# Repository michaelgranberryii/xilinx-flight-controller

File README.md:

# Xilinx Zynq-7000 Flight Controller 

This is a custom flight controller for a quadcopter drone, implemented on a Zynq-7000 SoC on the [Zybo Z7-10 FPGA SoC Development Board](https://digilent.com/shop/zybo-z7-zynq-7000-arm-fpga-soc-development-board/?gad_source=1&gclid=Cj0KCQiAkeSsBhDUARIsAK3tiedDBNo96Tg5VWCeuEqzXgPKJSFg8GQ0qwLCV-v5TlTKltLerrQGLDkaAjBgEALw_wcB). The flight controller uses PID controllers along with a [MPU-6050 | 3 Axis Accelerometer Gyroscope ](https://www.amazon.com/HiLetgo-MPU-6050-Accelerometer-Gyroscope-Converter/dp/B01DK83ZYQ?th=1) for flight stability. Two flight modes are available: Rate Mode (Acro Mode) which uses a single loop PID controller and Stabilize Mode (Self-Leveling Mode) which uses a dual loop PID controller.

## Dependencies

### Hardware

* [Zybo Z7-10 FPGA SoC Development Board](https://digilent.com/shop/zybo-z7-zynq-7000-arm-fpga-soc-development-board/?gad_source=1&gclid=Cj0KCQiAkeSsBhDUARIsAK3tiedDBNo96Tg5VWCeuEqzXgPKJSFg8GQ0qwLCV-v5TlTKltLerrQGLDkaAjBgEALw_wcB)
* [MPU-6050 | 3 Axis Accelerometer Gyroscope ](https://www.amazon.com/HiLetgo-MPU-6050-Accelerometer-Gyroscope-Converter/dp/B01DK83ZYQ?th=1)
* [Radiolink T8FB 8 Channels 2.4GHz RC Remote Transmitter and R8EF Receiver](https://www.amazon.com/Radiolink-Transmitter-Receiver-2-4GHz-Controller/dp/B07DPK9Q9X/ref=sr_1_8?crid=34H23UYBP2SKA&dib=eyJ2IjoiMSJ9.DPB_D_-uXEtxyzGycjiEyngkkrfimBVfbW4ewKRMgHdWoZd8kxR5b7jw0f5nMZls2Qb6V5CaN3ZfWsz7HZxhJrX90tzAb0QPEJUbYPUGGb2kpEbRmFlTLI2P86QUEIuNXMQfID7UFSSD-5kdgcvyu__B-VTDg-fb5czwKHN0Wl5XwdQDziz_BhiWEbAXvPp5PIw9FovmLC-oN_uPQwk0yAiQCDHy_djiuKr69YO0ViHIPJ16aY1Z_osZuZJMaIu-6asyX8v1I-ymjkhxUaAazSm7HCGohjngMDOZZgtEtbo.cCZTWbZ4u9XV9URevBCROmEVp4g-vu0lXmYiJxgRPmQ&dib_tag=se&keywords=drone+transmitter+radiolink&qid=1708402155&sprefix=drone+transmitter+radiolink%2Caps%2C165&sr=8-8)
* [F450 Drone Frame](https://www.amazon.com/HAWKS-WORK-Quadcopter-Soldered-version/dp/B09YQ4G4ZZ/ref=sr_1_1_sspa?crid=3N3WTXPM9LDKL&dib=eyJ2IjoiMSJ9.4SM5ot4VWDgjLdCVw62C2yKGLYTUUuc3lbi4BrTFGE9lpAKh0yMmMXJ_HIy-w1ENHsgIOVhhmYWpFB1ATbVhs8RRjUUaeWzyVOR1N0ha3JY5y-i-1TJu3e379htrydVJESWKMowWwq3ruebfXOp-SGRewwEUEbb5dCo8WSYisElMiAdD_meuExWMUxu_mJaVYU8nyTCTg59dAqnkI0jdbjbaDX142WhmPunSSgKYpJLF43dOjwTOQLx0ovp_XpcfKXJkWCgRW7E7xXokXZvfmimUiE6o6ibQ7mAoeM-98c8.ubOFJzHZ3AU_jyVGw8lJqdBcv9VBNKbAPPYqhvaB-e4&dib_tag=se&keywords=f450%2Bdrone%2Bframe&qid=1708402234&sprefix=f450%2Bdrone%2Caps%2C195&sr=8-1-spons&sp_csd=d2lkZ2V0TmFtZT1zcF9hdGY&th=1)
* [30A RC Brushless Motor Electric Speed Controller](https://www.amazon.com/RC-Brushless-Electric-Controller-bullet/dp/B071GRSFBD/ref=sr_1_4?crid=JMXOMHTAUCHV&dib=eyJ2IjoiMSJ9.wcXRcC8u6WMTk321CJMspA4Bjo8WyvU7S9tdHj4XXrRZN6O7hHFl5kzbjSvzMTZ-En1jRhSm3J4cd7zgXAknn8JgPXHhCurCiWyFo9wgS5pcgzPpAIhjxL9Zowfe-L6ReOSvZWRXDYMergQ2oleuHK2eYooR3kCsa7zb9R_QjHrUg5n7qfPdMynH9s7QN47VYThoIomzGBI9prRIGsj_hF-og1T7GlsKNxmGigtNDy_M2_I7ierAaly00huwBsoYgW8GAUCkMK90ynJmFmaWF3O137GK70m53xuhO36fMbs.yiFtRNF5yDGhqlkxH_yx9H00WZNZ_0crOrciYLcckoY&dib_tag=se&keywords=30A%2BRC%2BBrushless%2BMotor%2BElectric%2BSpeed%2BController%2BESC%2B3A%2BUBEC%2Bwith%2BXT60%2B%26%2B3.5mm%2BBullet%2BPlugs&qid=1708402480&sprefix=30a%2Brc%2Bbrushless%2Bmotor%2Belectric%2Bspeed%2Bcontroller%2Besc%2B3a%2Bubec%2Bwith%2Bxt60%2B%26%2B3.5mm%2Bbullet%2Bplugs%2Caps%2C155&sr=8-4&th=1)
* [A2212 1000KV Brushless Motor](https://www.amazon.com/QWinOut-Brushless-Outrunner-Multi-Copter-Quadcopter/dp/B07CVDHQKS/ref=sr_1_1?crid=1G5IM8DKU8SIP&dib=eyJ2IjoiMSJ9._27XAJ6z8Xiract4kND7udNpiqoN_pQC9MedRzfhIFYGyRx9oyV5UhlLUdA22XvwF8kf8OSVQj0Fo-E9RT67TuAs-i4kOSFeHEzr5NU0mvVaUnKGs5Vf8deE6-NLwU4lUR9LpMEcDlGJF7BHMjlHVvMGppm1qU6BHaiMaZuR91UzML-gfybXsLUigy1LmJ-3tyF6_1ikHYOK8w0fWH6f9ZbS-gAenApGc8AXPPVziHve8GzoEiNgXvsa65UJDh4SNVLwRSYLvnt5_zQseZ6h8uqAZkQQI8VzSBp9jZAkarI.3QyAjjS6RmnuF1MkatmTFHBwq5IZlhVe7zZr4WBPnxk&dib_tag=se&keywords=QWinOut%2BA2212%2B1000KV%2BBrushless%2BOutrunner%2BMotor%2B13T%2Bwith%2B3.5mm%2BMale%2BBanana%2BBullet%2Bfor%2BRC%2BDIY%2BAircraft%2BMulti-Copter%2BQuadcopter%2BDrone%2B(1%2BPcs)&qid=1708402578&sprefix=qwinout%2Ba2212%2B1000kv%2Bbrushless%2Boutrunner%2Bmotor%2B13t%2Bwith%2B3.5mm%2Bmale%2Bbanana%2Bbullet%2Bfor%2Brc%2Bdiy%2Baircraft%2Bmulti-copter%2Bquadcopter%2Bdrone%2B1%2Bpcs%2B%2Caps%2C229&sr=8-1&th=1)

### Software

* [Xilinx Vivado](https://www.xilinx.com/products/design-tools/vivado.html)
* [Xilinx Vitis](https://www.xilinx.com/products/design-tools/vitis.html)

## Demo Video

* [Youtube Video Demo: Flight Test](https://youtu.be/FbfccM_4fSk?si=GJgJV7dLbOb1_a_V)
* [Youtube Video Demo: Mini Flight Test and KiCAD PCB Test](https://youtu.be/7qQ3-POSWRU)
* [Youtube Video Demo: PID Controller Test](https://youtu.be/jsMdaXCYHB4)

## Images

Additional sensors (barometer, GPS, magnetometer, camera, etc.) are being integrated to enable features such as altitude hold, position hold, and object avoidance/detection.

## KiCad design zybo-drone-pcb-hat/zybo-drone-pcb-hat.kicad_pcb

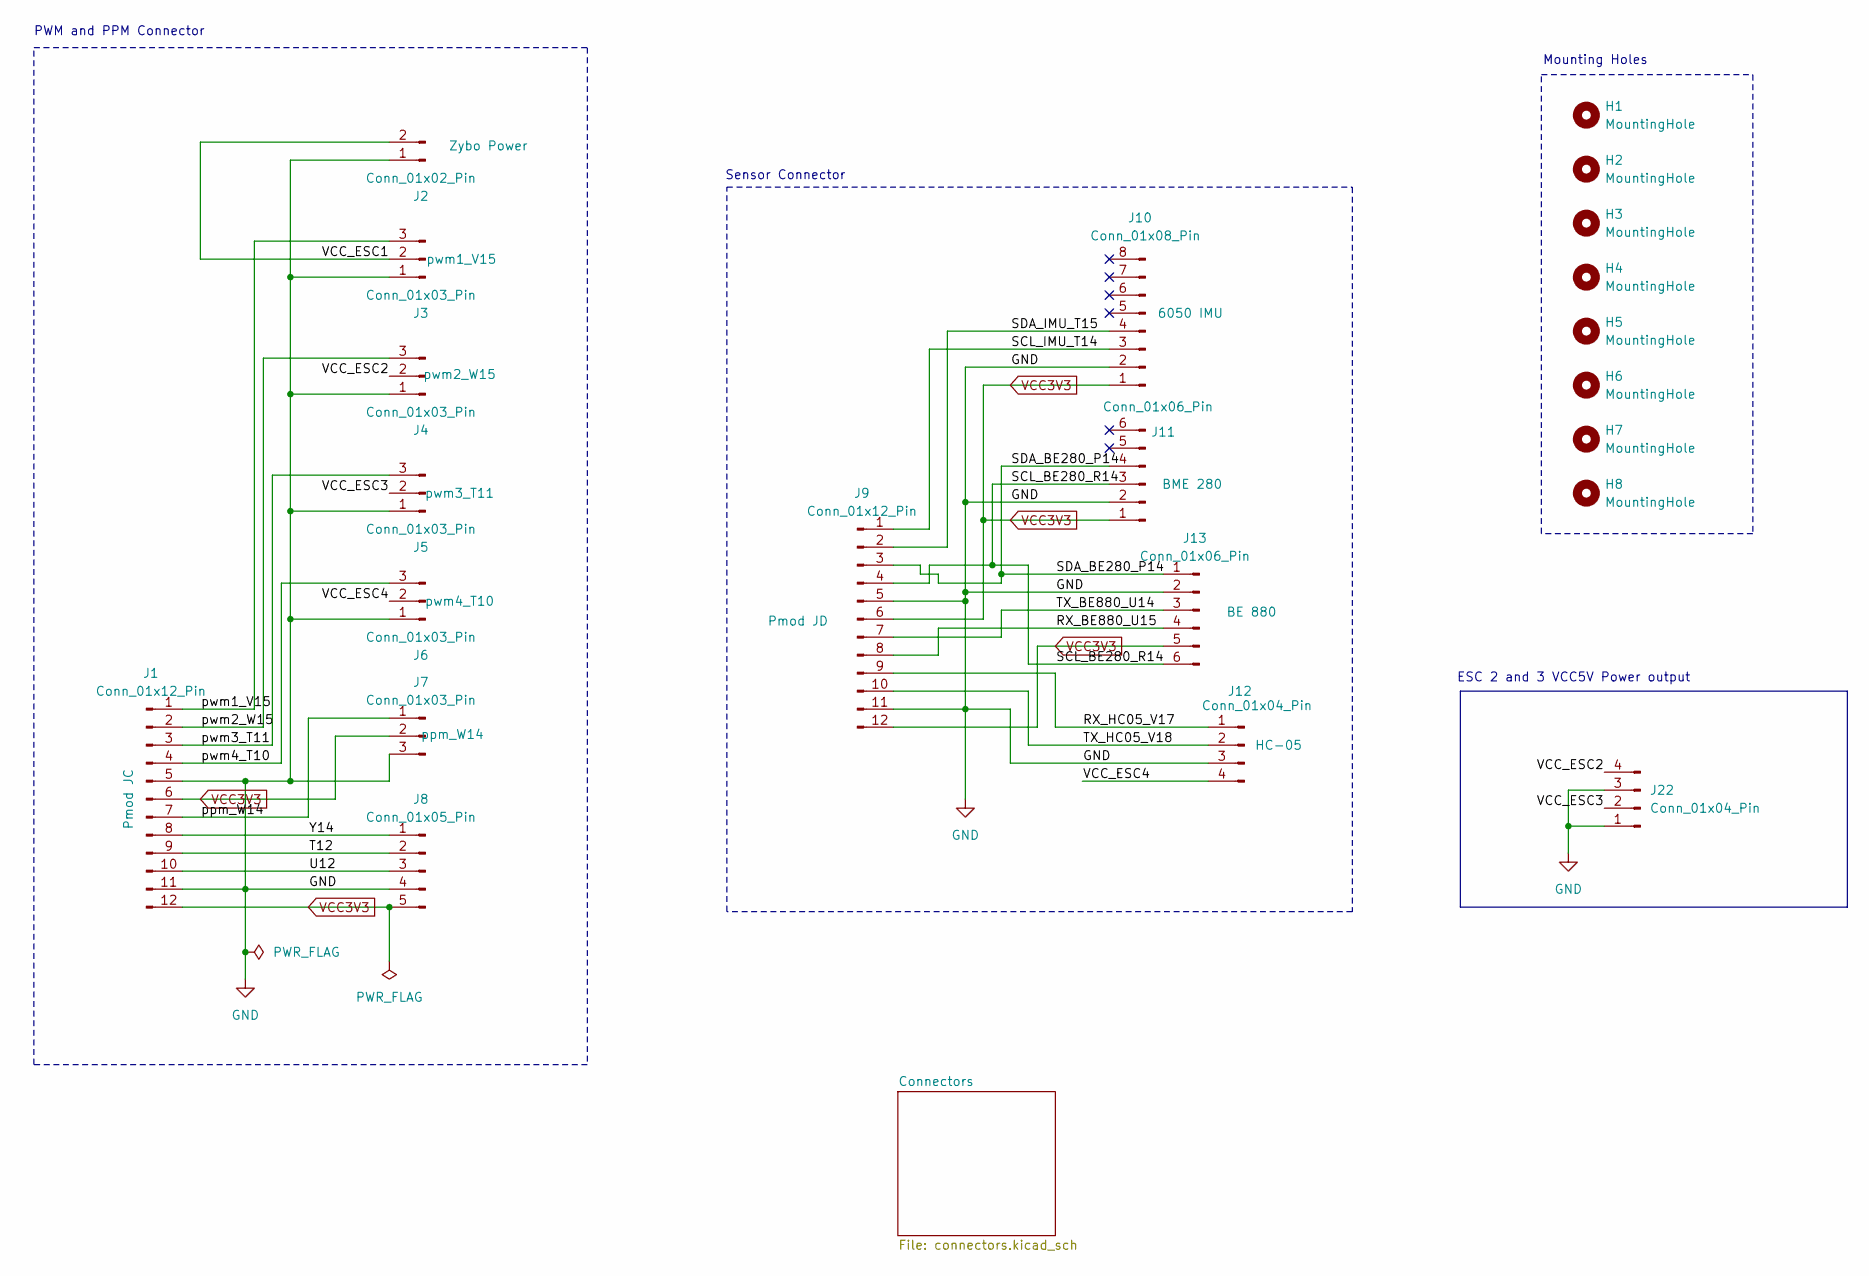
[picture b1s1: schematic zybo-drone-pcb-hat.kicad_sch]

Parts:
H1, H2, H3, H4, H5, H6, H7, H8: MountingHole; MountingHole_3.2mm_M3
J1, J9: Conn_01x12_Pin; PinSocket_2x06_P2.54mm_Vertical_zybo_mod
J2: Conn_01x02_Pin; PinHeader_1x02_P2.54mm_Horizontal
J3, J4, J5, J6, J7: Conn_01x03_Pin; PinHeader_1x03_P2.54mm_Horizontal
J8: Conn_01x05_Pin; PinHeader_1x05_P2.54mm_Horizontal
J10: Conn_01x08_Pin; PinSocket_1x08_P2.54mm_Horizontal
J11: Conn_01x06_Pin; PinSocket_1x06_P2.54mm_Horizontal
J12: Conn_01x04_Pin; PinSocket_1x04_P2.54mm_Horizontal
J13: Conn_01x06_Pin; PinHeader_1x06_P2.54mm_Horizontal
J22: Conn_01x04_Pin; PinHeader_2x02_P2.54mm_Horizontal

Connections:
/RX_BE880_U15: J9.8, J13.4
/RX_HC05_V17: J9.9, J12.1
/SCL_BE280_R14: J9.4, J11.3, J13.6
/SCL_IMU_T14: J9.1, J10.3
/SDA_BE280_P14: J9.3, J11.4, J13.1
/SDA_IMU_T15: J9.2, J10.4
/T12: J1.9, J8.2
/TX_BE880_U14: J9.7, J13.3
/TX_HC05_V18: J9.10, J12.2
/U12: J1.10, J8.3
/VCC_ESC1: J2.2, J3.2
/VCC_ESC2: J4.2, J22.4
/VCC_ESC3: J5.2, J22.2
/VCC_ESC4: J6.2, J12.4
/Y14: J1.8, J8.1
/ppm_W14: J1.7, J7.1
/pwm1_V15: J1.1, J3.3
/pwm2_W15: J1.2, J4.3
/pwm3_T11: J1.3, J5.3
/pwm4_T10: J1.4, J6.3
GND: J1.5, J1.11, J2.1, J3.1, J4.1, J5.1, J6.1, J7.3, J8.4, J9.5, J9.11, J10.2, J11.2, J12.3, J13.2, J22.1, J22.3; also elsewhere on the board
VCC3V3: J1.6, J1.12, J7.2, J8.5, J9.6, J9.12, J10.1, J11.1, J13.5; also elsewhere on the board

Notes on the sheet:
PWM and PPM Connector
ESC 2 and 3 VCC5V Power output
Mounting Holes
Sensor Connector

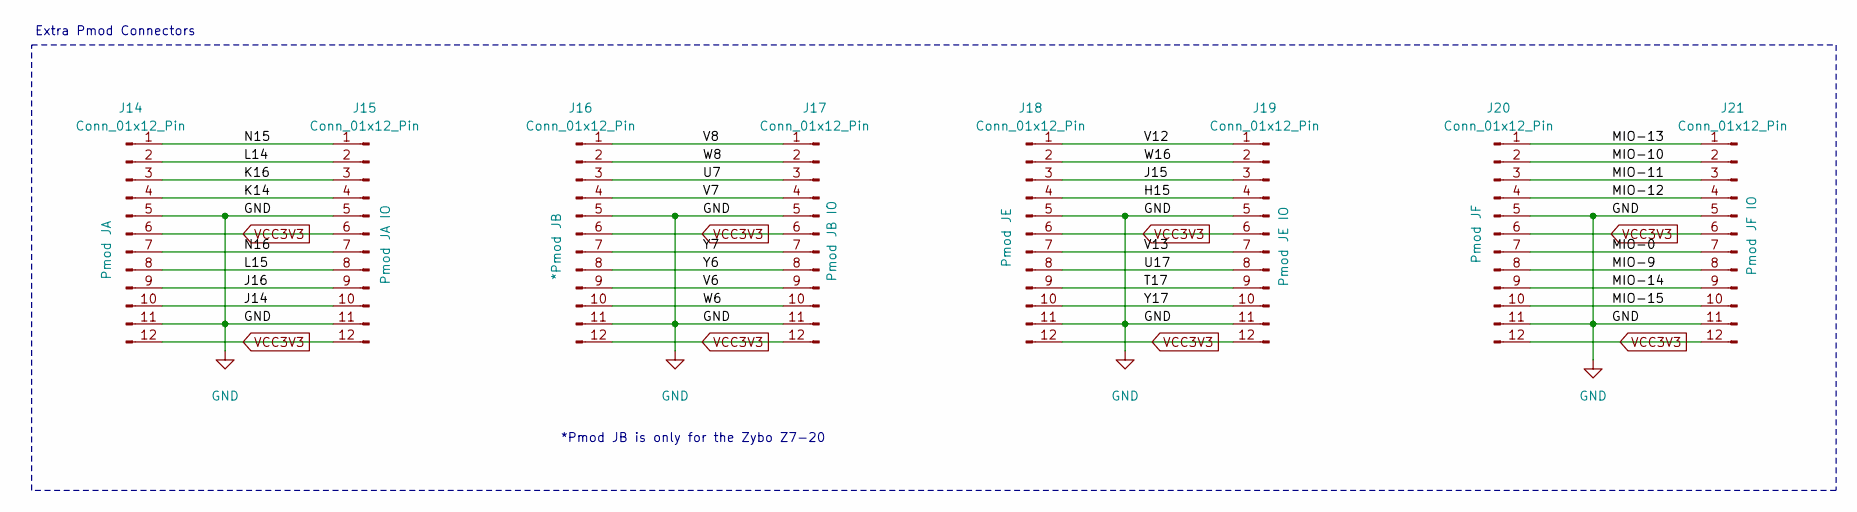
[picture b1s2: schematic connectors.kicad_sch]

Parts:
J14, J16, J18, J20: Conn_01x12_Pin; PinSocket_2x06_P2.54mm_Vertical_zybo_mod
J15, J17, J19, J21: Conn_01x12_Pin; PinHeader_2x06_P2.54mm_Horizontal_zybo_mod

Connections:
/Connectors/H15: J18.4, J19.4
/Connectors/J14: J14.10, J15.10
/Connectors/J15: J18.3, J19.3
/Connectors/J16: J14.9, J15.9
/Connectors/K14: J14.4, J15.4
/Connectors/K16: J14.3, J15.3
/Connectors/L14: J14.2, J15.2
/Connectors/L15: J14.8, J15.8
/Connectors/MIO-0: J20.7, J21.7
/Connectors/MIO-9: J20.8, J21.8
/Connectors/MIO-10: J20.2, J21.2
/Connectors/MIO-11: J20.3, J21.3
/Connectors/MIO-12: J20.4, J21.4
/Connectors/MIO-13: J20.1, J21.1
/Connectors/MIO-14: J20.9, J21.9
/Connectors/MIO-15: J20.10, J21.10
/Connectors/N15: J14.1, J15.1
/Connectors/N16: J14.7, J15.7
/Connectors/T17: J18.9, J19.9
/Connectors/U7: J16.3, J17.3
/Connectors/U17: J18.8, J19.8
/Connectors/V6: J16.9, J17.9
/Connectors/V7: J16.4, J17.4
/Connectors/V8: J16.1, J17.1
/Connectors/V12: J18.1, J19.1
/Connectors/V13: J18.7, J19.7
/Connectors/W6: J16.10, J17.10
/Connectors/W8: J16.2, J17.2
/Connectors/W16: J18.2, J19.2
/Connectors/Y6: J16.8, J17.8
/Connectors/Y7: J16.7, J17.7
/Connectors/Y17: J18.10, J19.10
GND: J14.5, J14.11, J15.5, J15.11, J16.5, J16.11, J17.5, J17.11, J18.5, J18.11, J19.5, J19.11, J20.5, J20.11, J21.5, J21.11; also elsewhere on the board
VCC3V3: J14.6, J14.12, J15.6, J15.12, J16.6, J16.12, J17.6, J17.12, J18.6, J18.12, J19.6, J19.12, J20.6, J20.12, J21.6, J21.12; also elsewhere on the board

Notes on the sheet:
*Pmod JB is only for the Zybo Z7-20
Extra Pmod Connectors

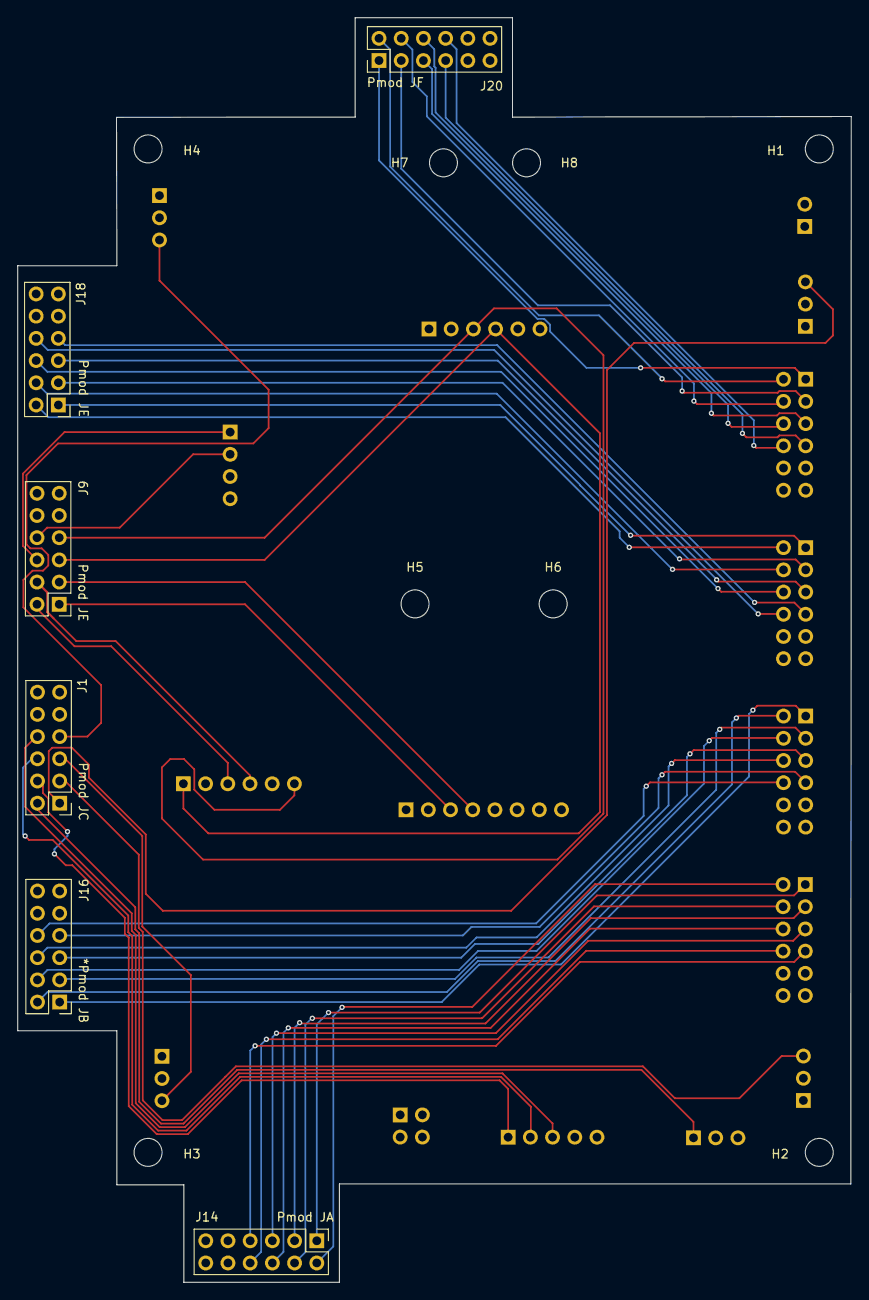
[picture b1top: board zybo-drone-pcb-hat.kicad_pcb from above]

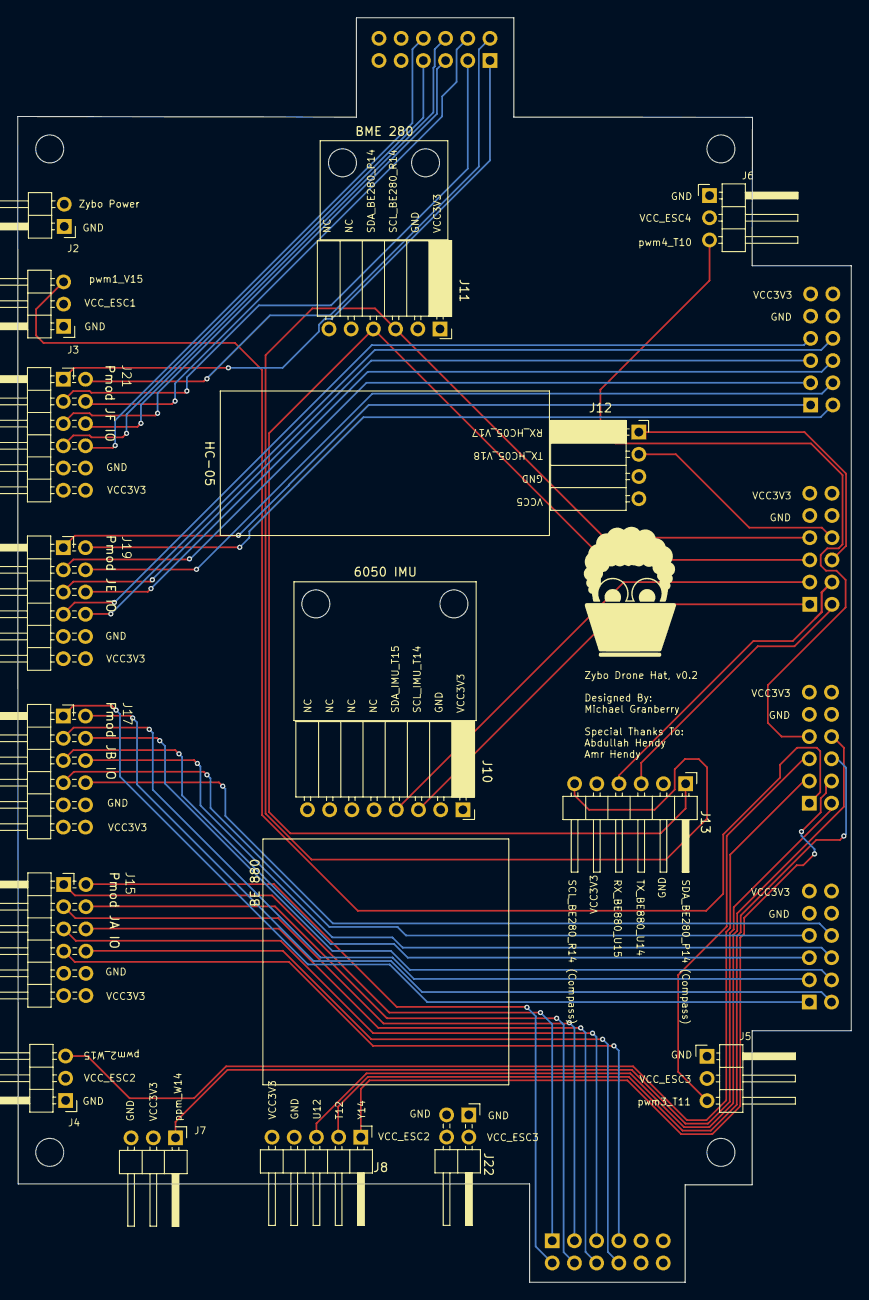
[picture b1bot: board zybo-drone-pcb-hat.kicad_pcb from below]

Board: 4 copper layers, 95.3 x 144.7 mm, 30 parts (12 on the bottom side), 54 nets.

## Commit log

2024-06-23 init commit of public code
2024-06-23 removed FIR filter
2024-06-30 added KiCAD PCB
2024-06-30 added images and updated readme
